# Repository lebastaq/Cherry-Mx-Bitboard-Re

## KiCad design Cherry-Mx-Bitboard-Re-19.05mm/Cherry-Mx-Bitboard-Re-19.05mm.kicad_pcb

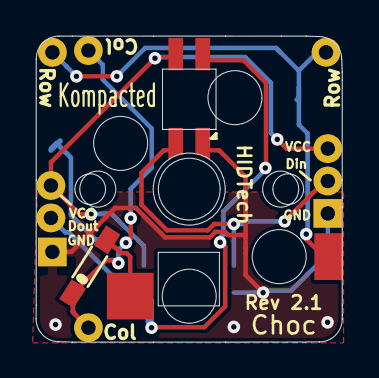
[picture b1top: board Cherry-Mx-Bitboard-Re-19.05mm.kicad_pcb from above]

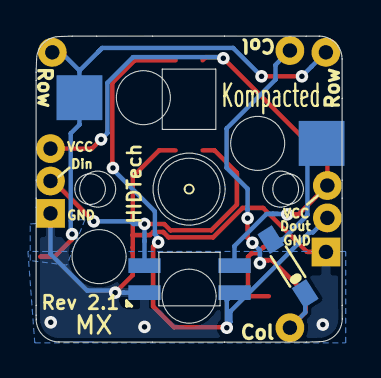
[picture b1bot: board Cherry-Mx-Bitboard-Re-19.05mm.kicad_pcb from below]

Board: 2 copper layers, 17.0 x 17.0 mm, 16 parts (5 on the bottom side), 7 nets.

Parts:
Col112, Col113: Conn_01x01; Wirepad
D2, D3: 1N4148W
D5, D6: SK6812MINI_E; YS-SK6812MINI-E_REVERSE
Din1: Conn_01x01; Wirepad
Dout1: Conn_01x01; Wirepad
GND1, GND2: Conn_01x01; Wirepad
Row111, Row113: Conn_01x01; Wirepad
SW1: SW_Push; CherryMx_Socket
SW2: SW_Push-Switch; Kailh_socket_PG1350
Vcc1, Vcc2: Conn_01x01; Wirepad

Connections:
Col1: Col112.1, Col113.1, D2.1, D3.1
Din: D5.4, D6.4, Din1.1
Dout: D5.2, D6.2, Dout1.1
GND: D5.3, D6.3, GND1.1, GND2.1
unnamed: D2.2, D3.2, SW1.1, SW2.1
Row1: Row111.1, Row113.1, SW1.2, SW2.2
VCC: D5.1, D6.1, Vcc1.1, Vcc2.1

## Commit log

2020-05-03 added choc
2020-05-04 add rgb leds
2020-05-04 simplified
2020-05-04 fix both sides rgb leds
2020-05-04 fix holes on both sides
2020-05-04 flip leds so they face the right side
2020-05-04 add custom footprint
2020-05-05 Cleaned up
2020-05-05 Silk
2020-05-05 Break tabs
2020-05-05 Plate generaged with gerber
2020-05-05 gerber.zip
2020-05-05 routing
2020-05-06 fix DRC errors: zone priority
2020-05-06 add plaque
2020-06-04 switch to sk6812 mini-e
